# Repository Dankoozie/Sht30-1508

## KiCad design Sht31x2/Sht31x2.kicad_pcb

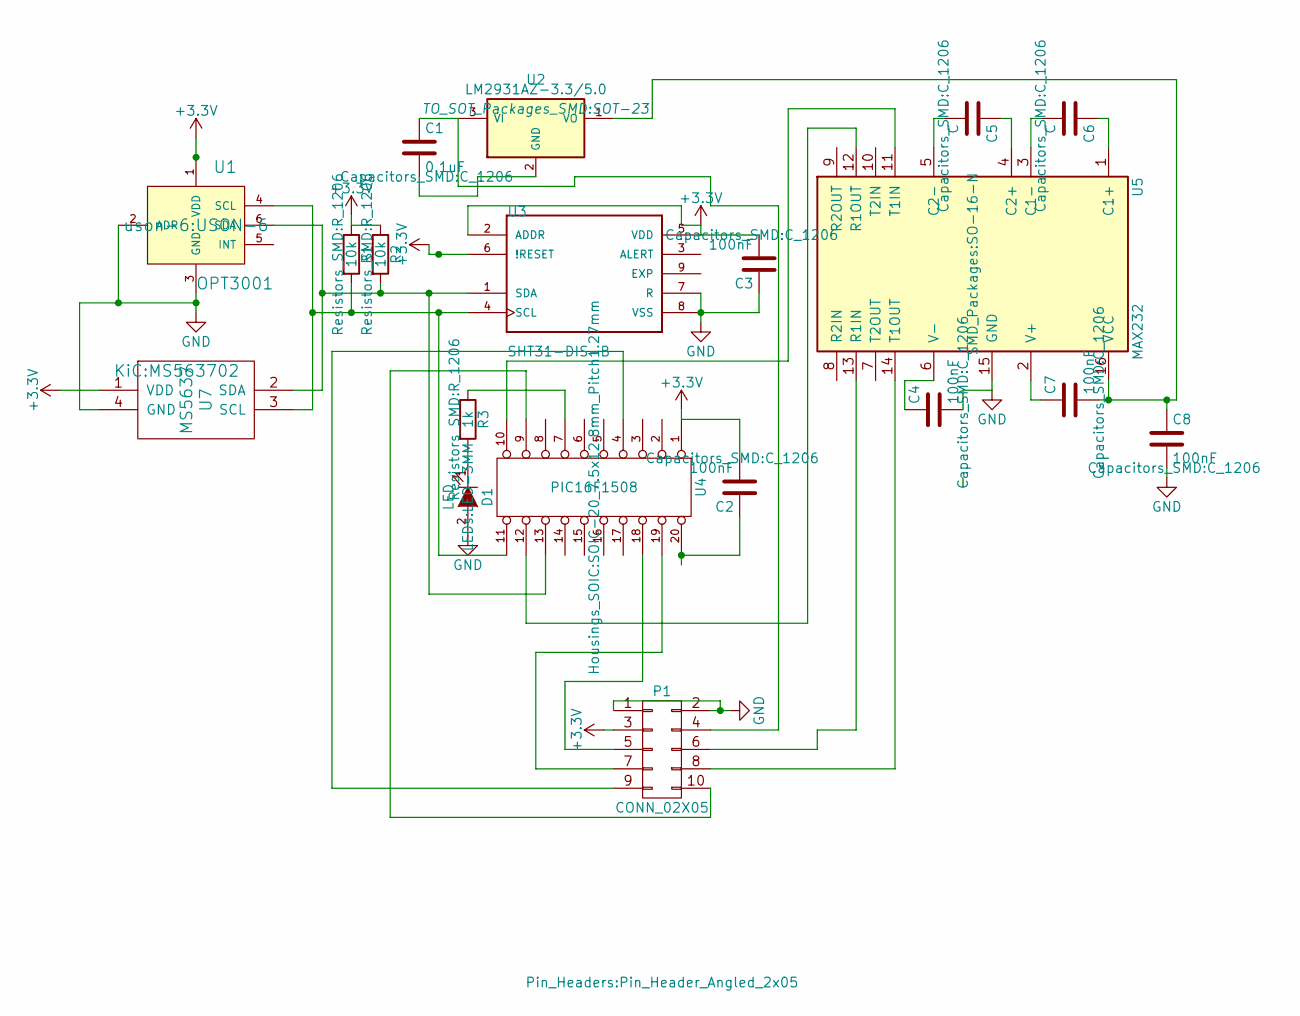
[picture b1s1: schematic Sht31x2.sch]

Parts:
C1: 0.1uF; C_1206
C2, C3, C4, C7, C8: 100nF; C_1206
C5, C6: C; C_1206
D1: LED; LED-3MM
P1: CONN_02X05; Pin_Header_Angled_2x05
R1, R2: 10k; R_1206
R3: 1k; R_1206
U1: OPT3001; USON-6
U2: LM2931AZ-3.3/5.0; SOT-23
U3: SHT31-DIS-B; SON50P250X250X100-9N
U4: PIC16F1508; SOIC-20_7.5x12.8mm_Pitch1.27mm
U5: MAX232; SO-16-N
U7: MS5637; MS563702

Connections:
+3V3: C2.2, C3.2, P1.3, R1.1, R2.1, U1.1 (VDD), U3.2 (ADDR), U3.5 (VDD), U3.6 (!RESET), U4.1, U7.1 (VDD)
GND: C3.1, C4.2, C8.2, D1.2 (A), P1.1, P1.2, U1.2 (ADR), U1.3 (GND), U3.7 (R), U3.8 (VSS), U5.15 (GND), U7.4 (GND)
unnamed: C1.1, P1.4, U2.3 (VI)
unnamed: C1.2, U2.2 (GND)
unnamed: C2.1, U4.20
unnamed: C4.1, U5.6 (V-)
unnamed: C5.1, U5.4 (C2+)
unnamed: C5.2, U5.5 (C2-)
unnamed: C6.1, U5.1 (C1+)
unnamed: C6.2, U5.3 (C1-)
unnamed: C7.1, U5.2 (V+)
unnamed: C7.2, C8.1, U2.1 (VO), U5.16 (VCC)
unnamed: D1.1 (K), R3.2
unnamed: P1.5, U4.18
unnamed: P1.6, U5.13 (R1IN)
unnamed: P1.7, U4.19
unnamed: P1.8, U5.14 (T1OUT)
unnamed: P1.9, U4.4
unnamed: P1.10, U4.9
unnamed: R1.2, U1.4 (SCL), U3.4 (SCL), U4.11, U7.3 (SCL)
unnamed: R2.2, U1.6 (SDA), U3.1 (SDA), U4.13, U7.2 (SDA)
unnamed: R3.1, U4.7
unnamed: U4.10, U5.11 (T1IN)
unnamed: U4.12, U5.12 (R1OUT)

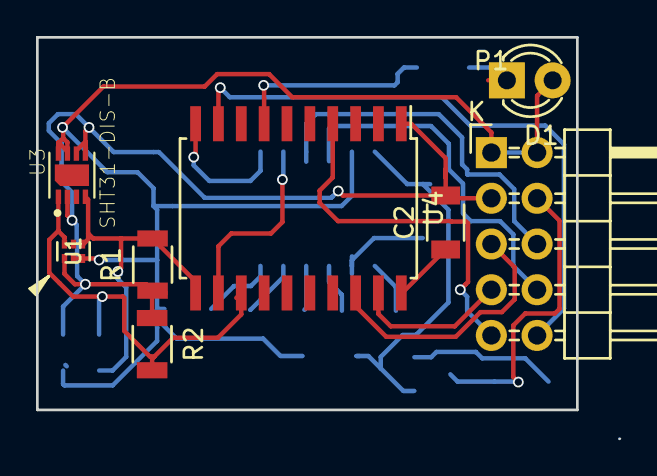
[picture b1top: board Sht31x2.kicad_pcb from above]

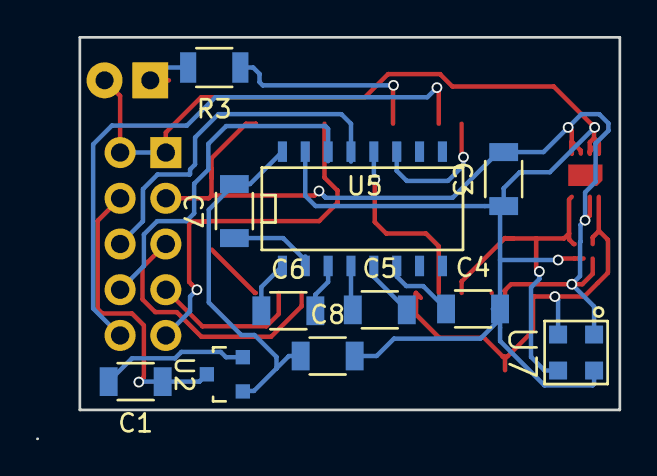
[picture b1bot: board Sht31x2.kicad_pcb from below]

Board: 2 copper layers, 32.4 x 22.3 mm, 19 parts (11 on the bottom side), 24 nets.

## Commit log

2015-11-14 Initial
2015-11-19 add humidity and temp functions
2015-11-20 Add struct,read functions
2015-11-21 calc crc
2015-11-23 move i2c stuff to i2c.c/h
2015-11-23 output ansi colours, default baud 1200
2015-11-28 Clear status & heater functions
2017-01-09 add pcb files
